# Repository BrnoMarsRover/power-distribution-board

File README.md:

# Power distribution board

Everything for the BrnoMarsRover power distribution board: the schematic and PCB, the
firmware that runs on it, and the ROS 2 driver that consumes it.

```
kicad/      schematic and PCB
pdf/        exported schematics
firmware/   Raspberry Pi Pico 2 sketch (Arduino, arduino-pico core)
ros2/       ROS 2 driver package (ament_python, Humble)
```

The firmware and the driver live together **because they share a versioned wire
protocol**. Every field name and status bit below is written twice - once in
`firmware/PowerBoard/Functions.cpp` and once in `ros2/powerboard/powerboard/powerboard_node.py`.
Splitting them across repositories would let the two halves be changed, reviewed and
deployed independently, and the failure mode is not a build error - it is silently
misparsed telemetry. Change the protocol in one commit, and bump `jsonSchemaVersion`
(firmware `Config.cpp`) together with `SUPPORTED_SCHEMA` (node) when you do.

## Hardware

Five INA238 current/voltage monitors on I2C, one per branch, each with a high-side
switch:

| Designator | I2C  | Shunt  | Rail             | Limit   |
|-----------|------|--------|------------------|---------|
| U2        | 0x40 | 3 mOhm | battery feed, and the master gate for the rest | 15 A |
| U3        | 0x41 | 5 mOhm | 24 V             | 2.5 A   |
| U4        | 0x42 | 5 mOhm | 15 V             | 4 A     |
| U5        | 0x43 | 5 mOhm | 12 V             | 5 A     |
| U6        | 0x44 | 5 mOhm | 5 V              | 12 A    |

Limits come from the 60 W rating of each DC-DC converter.

**Over-current protection ships disabled** (`ocpEnabled = false`). Some high-side
drivers were tripped by inrush and are bridged, so the board cannot actually switch
those branches off. Limits are still evaluated and reported, so an overload is visible
in telemetry even though nothing acts on it. `OCP ON` enables tripping if the hardware
is ever repaired.

Two things the board cannot measure, by construction:

- **Charging current.** The charger is wired on the battery side of U2's shunt, so
  charge current never crosses it. The driver infers charging from rising open-circuit
  voltage instead.
- **Currents above ~8 A on the INA CURRENT register**, which saturates there. The
  shunt-derived value is used for protection and for the `i` field because it has the
  range; `ir` is kept alongside it only for cross-checking.

## Serial protocol (schema v1)

USB CDC-ACM, one JSON object per line, telemetry at 2 Hz. Anything not starting with
`{` is human-readable diagnostics (`STATUS`, `RAW`) and is ignored by machine readers.

`"t"` gives the line type: `tel`, `evt`, `ack`, `err`, `info`.

### `tel` - periodic telemetry

```json
{"t":"tel","v":1,"seq":123,"up":61500,"ocp":0,"mst":1,"b":[ ... ]}
```

| Key   | Meaning                                        |
|-------|------------------------------------------------|
| `v`   | schema version                                  |
| `seq` | frame counter; gaps mean frames were lost       |
| `up`  | milliseconds since board boot                   |
| `ocp` | 1 if over-current protection is enabled         |
| `mst` | 1 if the U2 master branch is on                 |
| `b`   | one object per branch                           |

Each branch object:

| Key   | Unit | Meaning                                                   |
|-------|------|-----------------------------------------------------------|
| `n`   |      | designator, `U2`..`U6`                                    |
| `a`   |      | I2C address                                               |
| `s`   |      | status bits, see below                                    |
| `lim` | mA   | configured current limit                                  |
| `vb`  | V    | bus voltage                                               |
| `vs`  | mV   | shunt voltage                                             |
| `i`   | mA   | current derived from the shunt - **this is the real one** |
| `ir`  | mA   | INA CURRENT register, saturates at ~8 A, cross-check only |
| `tc`  | degC | INA die temperature                                       |
| `tr`  |      | cumulative trip count                                     |

Status bits in `s`:

| Bit  | Name        |
|------|-------------|
| 0x01 | online      |
| 0x02 | enabled     |
| 0x04 | tripped     |
| 0x08 | manual off  |
| 0x10 | powered     |
| 0x20 | over limit  |

### `evt` - pushed immediately, not on the telemetry tick

```json
{"t":"evt","up":61500,"ev":"over_limit","n":"U5","i":5200.0,"lim":5000,"ocp":0}
```

`ev` is one of `over_limit`, `over_limit_clear`, `ocp_trip`, `ocp_recover`. These are
pushed as they happen because with OCP disabled an over-limit event is the only
actionable signal the board can give.

### `ack` / `err` / `info`

```json
{"t":"ack","cmd":"JSON","msg":"json output"}
{"t":"err","cmd":"OFF U9","msg":"unknown branch"}
{"t":"info","fw":"...","v":1,"rails":5,"ocp":0}
```

### Commands (host to board, one per line)

| Command        | Effect                                          |
|----------------|-------------------------------------------------|
| `ON <U>`       | switch a branch on                              |
| `OFF <U>`      | switch a branch off                             |
| `OCP [ON|OFF]` | query or set over-current protection            |
| `RAW`          | dump every INA238 register, human readable      |
| `STATUS`       | human readable summary                          |
| `JSON`         | machine-readable output (the default)           |
| `HUMAN`        | switch to the plain-text table                  |
| `ONCE`         | emit a single telemetry frame                   |

## Firmware

Arduino sketch in `firmware/PowerBoard`, target Raspberry Pi Pico 2 (`rpipico2`),
arduino-pico core 5.5.1. Open `PowerBoard.ino` and flash it.

## ROS 2 driver

`ros2/powerboard`, ament_python, tested on Humble. Depends only on `rclpy`,
`std_msgs`, `sensor_msgs`, `diagnostic_msgs` and `python3-serial` - no custom
interfaces.

```bash
ros2 launch powerboard powerboard.launch.py
```

| Topic                | Type                       |
|----------------------|----------------------------|
| `~/battery`          | `sensor_msgs/BatteryState` |
| `~/rails/voltages`   | `std_msgs/Float32MultiArray` |
| `~/rails/currents`   | `std_msgs/Float32MultiArray` |
| `~/rails/powers`     | `std_msgs/Float32MultiArray` |
| `~/events`           | `std_msgs/String`          |
| `~/command`          | `std_msgs/String` (subscription, forwards any board command) |
| `/diagnostics`       | `diagnostic_msgs/DiagnosticArray` |

The rail arrays carry names in `layout.dim[i].label`, index-aligned with `data[i]`.

State of charge is estimated from a LiPo open-circuit-voltage curve, load-compensated
and smoothed, and published in `BatteryState.percentage`. It is a rough guide, not a
fuel gauge: between about 3.8 and 3.9 V/cell the curve is nearly flat, and below
3.7 V/cell it falls away sharply. Defaults assume Freya's **10S, 14.5 Ah** pack; see
`cell_count`, `design_capacity_ah` and `pack_resistance_ohm`.

**Only one process may hold the serial port.** Two readers steal bytes from each other,
which looks exactly like a flaky board - sequence gaps and a halved frame rate.

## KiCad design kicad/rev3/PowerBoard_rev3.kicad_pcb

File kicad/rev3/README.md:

# Power board rev3: KiCad 10 project

Open `PowerBoard_rev3.kicad_pro` in **KiCad 10**. The design spec lives in
[`docs/rev3/design.md`](../../docs/rev3/design.md), and every computed component value
comes from [`docs/rev3/rails.md`](../../docs/rev3/rails.md).

A review PDF is at [`pdf/rev3/PowerBoard_rev3_schematic.pdf`](../../pdf/rev3/PowerBoard_rev3_schematic.pdf).
The grouped BOM with part numbers is [`PowerBoard_rev3_bom.csv`](PowerBoard_rev3_bom.csv) (regenerate with `kicad-cli sch export bom`).
For the LCSC BOM tool, `python3 gen/bom_lcsc.py` turns it into [`PowerBoard_rev3_bom_lcsc.csv`](PowerBoard_rev3_bom_lcsc.csv) (MPN + manufacturer, no PCB-only items).

## How the schematic was made

`gen/build.py` generated it from the design data, so nothing was drawn by hand from
scratch:

```
python3 kicad/rev3/gen/build.py
```

That run does six things:

1. Writes the custom symbols (`PowerBoard_rev3.kicad_sym`).
2. Writes the custom footprints (`PowerBoard_rev3.pretty`).
3. Writes the 14 sheets.
4. Upgrades every file to the KiCad 10 format with `kicad-cli` (KiCad 10 from the `kicad-10.0-releases` PPA).
5. Runs ERC.
6. Exports KiCad's own netlist and checks it pin by pin against the netlist the script
   intended.

Result at generation time:
- 520 parts and 281 nets.
- Netlist check passes.
- ERC is clean at every severity.

Every sheet is drawn like a hand-made schematic: parts sit at chosen positions and real
wires connect them.
- Power flows left to right along the rails. Converters and drivers sit below their power
  path, with their setting parts below or beside them.
- Labels appear only where a signal leaves the sheet. The exception is the ESP32 module,
  whose GPIOs carry labels in the usual way, while the circuits around it (reset, boot,
  USB, host UART, LEDs, sense dividers) are drawn out.
- On the outputs sheet each rail is a column: a bus with one row per output (PTC,
  connector, GND).

The drawing goes through the same netlist check, so a wire landing where it shouldn't is
caught before anyone opens KiCad. One crossing is intentional: on the `can` sheet, CANH
crosses CANL without a junction on its way to the second connector.

## Board rules

`gen/board_rules.py` sets up the PCB side for JLCPCB's 4-layer process with 2 oz outer copper
(the one paid option):
- **Stackup:** 1.6 mm, JLC04161H-7628, 2 oz outer / 0.5 oz inner, HASL lead-free.
- **Limits:** 0.25 mm minimum track, 0.15 mm clearance, 0.25 mm annular ring (vias 0.9 / 0.4 mm
  and up), 1.0 mm silkscreen text.
- **Netclasses** for the 42 V, 54 V and rail nets, and a 0.5 mm clearance on the outer
  layers around 42 / 54 V pours.

It writes the rules into `PowerBoard_rev3.kicad_pro` and `PowerBoard_rev3.kicad_dru`.
It creates `PowerBoard_rev3.kicad_pcb` only if the board doesn't exist yet, so re-running
it never touches a layout. The values and the reasons for them are in
`docs/rev3/design.md`, section 8.

**Once you start editing in KiCad, these files are the source of truth.** Re-running
`build.py` overwrites them. The generator is a bootstrap, not a build step.

## Sheets

| Sheet | Contents |
|-------|----------|
| `power_in` | Battery XT90 input, SMCJ45A, bulk capacitance, 2 mΩ Kelvin shunt (Bourns CSS2H-2512K) with INA228, charger input XT60 and pack charge-port XT60 (charging flows through the shunt) |
| `sw_42d`, `sw_42c` | 42 V drive group and converter-feed group eFuses (TPS48111-Q1, 2 + 1 D2PAK). The drive group has the motor-switch kill FET on EN/UVLO. |
| `sw_24`, `sw_12`, `sw_5` | Rail eFuses, input TVS, bulk capacitance, input and output voltage sense |
| `sw_54` | eFuse in front of the 54 V boost |
| `brake` | Brake chopper on OUT42D: TLV1805 + LM4040 comparator (on 47.5 V, off 45 V), IPB042N10N3G, XT60 to an off-board braking resistor, BRAKE_ACT to the ESP32 |
| `outputs` | Rail input connectors, 8 × XT90 outputs, and the 24 / 12 / 5 V outputs with their PTCs. JST-XH 54 V output to the Zyxel |
| `boost54` | LM5122 boost, 30–42 V to 54 V, 100 W |
| `aux_power` | LM5017 (42 V to 5.3 V, constant on-time with ripple injection), the diode-OR with USB VBUS, and the AP7361C 3.3 V LDO |
| `mcu` | ESP32-S3-WROOM-1U, USB-C with ESD, host UART on JST-GH, buttons, LEDs, NTC |
| `can` | TCAN1044AV, split termination on solder jumpers, two Molex CLIK-Mate 4p CAN connectors matching the EPOS4 50/5 (X11 / X12) |
| `io` | TCA9535 (switch control), 2 × ADC128D818, motor-switch latch (74LVC1G74) and the rear-panel switch input |

## Custom parts

- **Symbols:** TPS48111-Q1, LM5122, LM5017, TLV1805, TCAN1044AV and INA228, with pinouts taken
  from the TI datasheets.
  - Their pins are arranged for the drawing. For example, the INA228 sense inputs sit on
    top, 5.08 mm apart under the shunt's sense pins, so the Kelvin lines drop straight down.
  - Q_NMOS_GDS covers the D2PAK and DPAK FETs: KiCad 10 dropped its GDS-numbered FET
    symbols.
- **Footprints:** R_Bourns_CSS2H-2512_Kelvin is Bourns' 4-terminal land pattern as a
  net-tie footprint. TI_DGX0019A_VSSOP-19 is drawn from TI's land pattern, with pads
  lengthened for hand soldering. XT90PB-M, XT90PB-F and DEANS-T are copied from rev2's
  SamacSys library.

## Review before layout

These are the things the generator could not settle on its own:

- [ ] **LM5122 loop.** R_SLOPE and the COMP–FB Type 2 network are computed in `rails.py`
  (crossover 8–11 kHz). Confirm on the bench with a load step from 0.2 to 1.8 A: the
  response should be damped, with no ringing.
- [x] **Pre-charge FET SOA.** Ramps were cut to stay inside the IPB042N10N3G's DC SOA
  (0.4 A at 42 V). See `docs/rev3/design.md` 4.3.
- [ ] **Bypass-link placement.** Put each eFuse's two bypass holes (M4 on the 42 V groups,
  M3 elsewhere) where a copper strip can be bolted across with the board in the rover,
  and silkscreen "BYPASS: no protection, battery off to fit".
- [ ] **EPOS4 input capacitance.** maxon doesn't publish it. Measure one drive: it sets the
  pre-charge ramp time (470 µF per drive is assumed).
- [ ] **Brake resistor.** Size the off-board resistor (10 Ω / 100 W assumed) to the
  rover's braking energy.
- [x] **Boost inductor footprint.** Coilcraft MSS1583-223MED on KiCad's `L_Coilcraft_MSS1583-XXX`.
- [ ] **Aux buck (LM5017).** On first power-up, check the switching frequency (about
  400 kHz) and that the FB ripple is clean, with no bursts of pulses followed by long gaps.
  Then check the output at 0 and 0.5 A. The Type 3 ripple values are TI's starting point.
- [ ] **Connector footprints.** XT90 and Deans: check the M and F pin geometry against the
  Amass drawings. For every power connector, check that footprint pin 1 is the housing's
  + side.
- [ ] **Electrolytic sizes.** 100 µF / 100 V and 100 µF / 80 V parts may need a larger
  footprint than `CP_Elec_10x10.5`.
- [ ] **Hand-solder holes.** Add a 1–1.5 mm plated hole through the exposed pads of the
  LM5122, the LM5017 and the ESP32 module (layout step).
- [ ] **Placement.** Put the MMBT3904 temperature sensors against their main FETs, and
  route every shunt Kelvin.
- [ ] **ESD arrays are flow-through.** On both USBLC6-2SC6, pins 1/6 and 3/4 are joined
  inside the part. The connector side and the MCU side are therefore separate nets, which
  forces each line across its pad pair in layout.

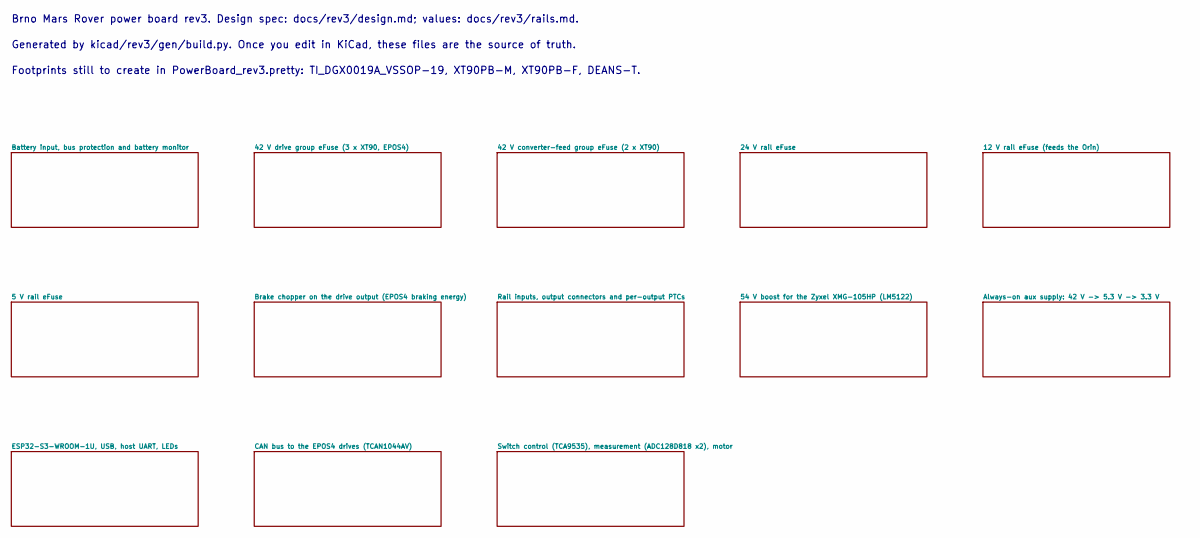
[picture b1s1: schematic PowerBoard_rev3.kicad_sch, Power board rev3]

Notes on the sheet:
Brno Mars Rover power board rev3. Design spec: docs/rev3/design.md; values: docs/rev3/rails.md.
Footprints still to create in PowerBoard_rev3.pretty: TI_DGX0019A_VSSOP-19, XT90PB-M, XT90PB-F, DEANS-T.
Generated by kicad/rev3/gen/build.py. Once you edit in KiCad, these files are the source of truth.

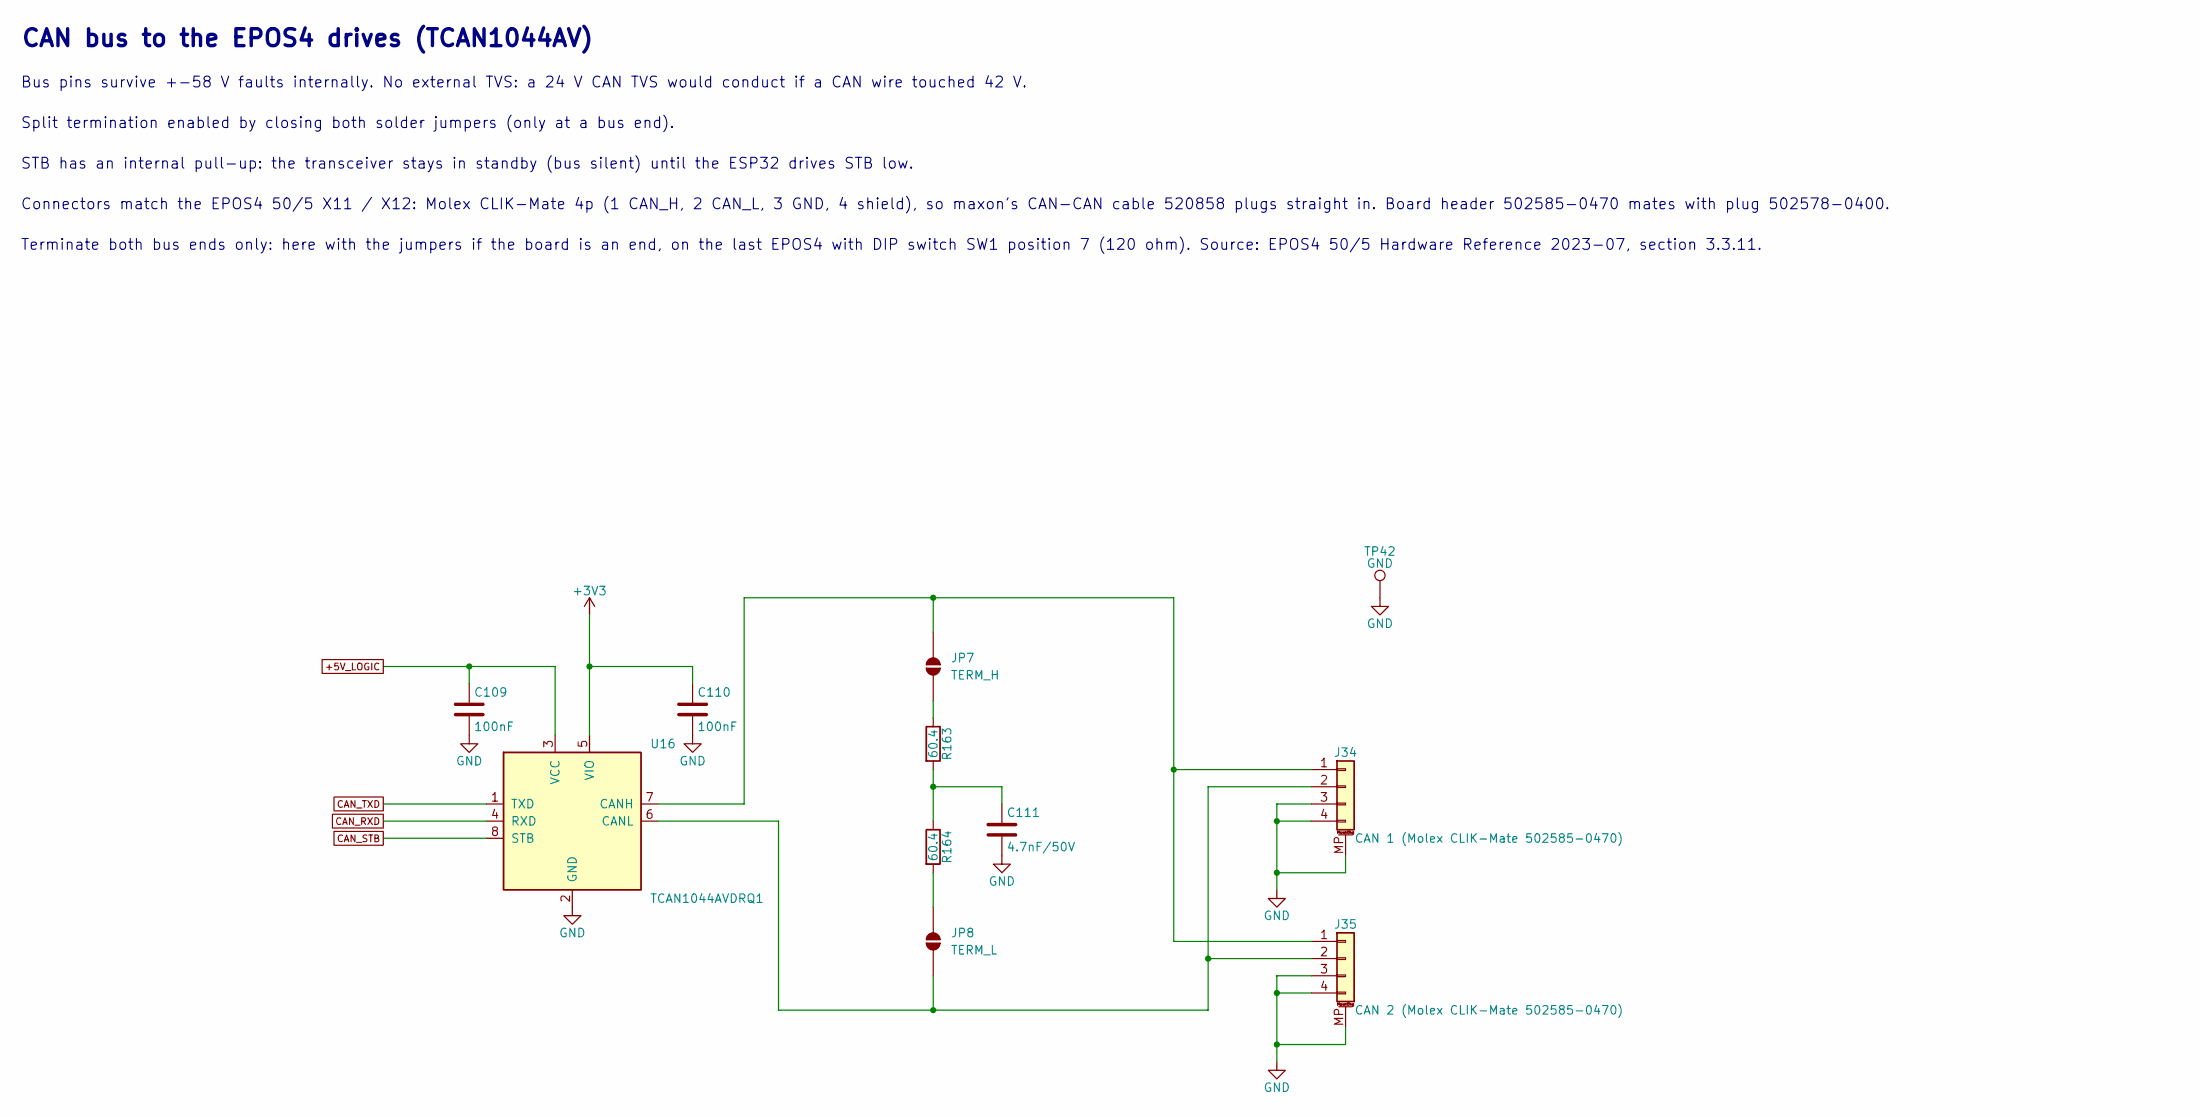
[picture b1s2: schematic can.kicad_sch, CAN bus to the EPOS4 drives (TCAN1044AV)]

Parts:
C109, C110: 100nF; C_0603_1608Metric_Pad1.08x0.95mm_HandSolder; MPN C0603C104K5RACTU
C111: 4.7nF/50V; C_0603_1608Metric_Pad1.08x0.95mm_HandSolder; MPN CL10B472KB8NNNC
J34: CAN 1 (Molex CLIK-Mate 502585-0470); Molex_CLIK-Mate_502585-0470_1x04-1MP_P1.50mm_Horizontal; MPN 502585-0470
J35: CAN 2 (Molex CLIK-Mate 502585-0470); Molex_CLIK-Mate_502585-0470_1x04-1MP_P1.50mm_Horizontal; MPN 502585-0470
JP7: TERM_H; SolderJumper-2_P1.3mm_Open_Pad1.0x1.5mm; MPN none: PCB solder jumper
JP8: TERM_L; SolderJumper-2_P1.3mm_Open_Pad1.0x1.5mm; MPN none: PCB solder jumper
R163, R164: 60.4; R_0805_2012Metric_Pad1.20x1.40mm_HandSolder; MPN ERJ-6ENF60R4V
TP42: GND; TestPoint_Keystone_5015_Micro_Mini; MPN 5015
U16: TCAN1044AVDRQ1; SOIC-8_3.9x4.9mm_P1.27mm; MPN TCAN1044AVDRQ1

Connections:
+3V3: C110.1, U16.5 (VIO); also elsewhere on the board
+5V_LOGIC: C109.1, U16.3 (VCC); also elsewhere on the board
CAN_RXD: U16.4 (RXD); also elsewhere on the board
CAN_STB: U16.8 (STB); also elsewhere on the board
CAN_TXD: U16.1 (TXD); also elsewhere on the board
GND: C109.2, C110.2, C111.2, J34.3, J34.4, J34.MP (MountPin), J35.3, J35.4, J35.MP (MountPin), TP42.1, U16.2 (GND); also elsewhere on the board
unnamed: C111.1, R163.2, R164.1
unnamed: J34.1, J35.1, JP7.1 (A), U16.7 (CANH)
unnamed: J34.2, J35.2, JP8.1 (A), U16.6 (CANL)
unnamed: JP7.2 (B), R163.1
unnamed: JP8.2 (B), R164.2

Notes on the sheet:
Bus pins survive +-58 V faults internally. No external TVS: a 24 V CAN TVS would conduct if a CAN wire touched 42 V.
Split termination enabled by closing both solder jumpers (only at a bus end).
Terminate both bus ends only: here with the jumpers if the board is an end, on the last EPOS4 with DIP switch SW1 position 7 (120 ohm). Source: EPOS4 50/5 Hardware Reference 2023-07, section 3.3.11.
CAN bus to the EPOS4 drives (TCAN1044AV)
Connectors match the EPOS4 50/5 X11 / X12: Molex CLIK-Mate 4p (1 CAN_H, 2 CAN_L, 3 GND, 4 shield), so maxon's CAN-CAN cable 520858 plugs straight in. Board header 502585-0470 mates with plug 502578-0400.
STB has an internal pull-up: the transceiver stays in standby (bus silent) until the ESP32 drives STB low.

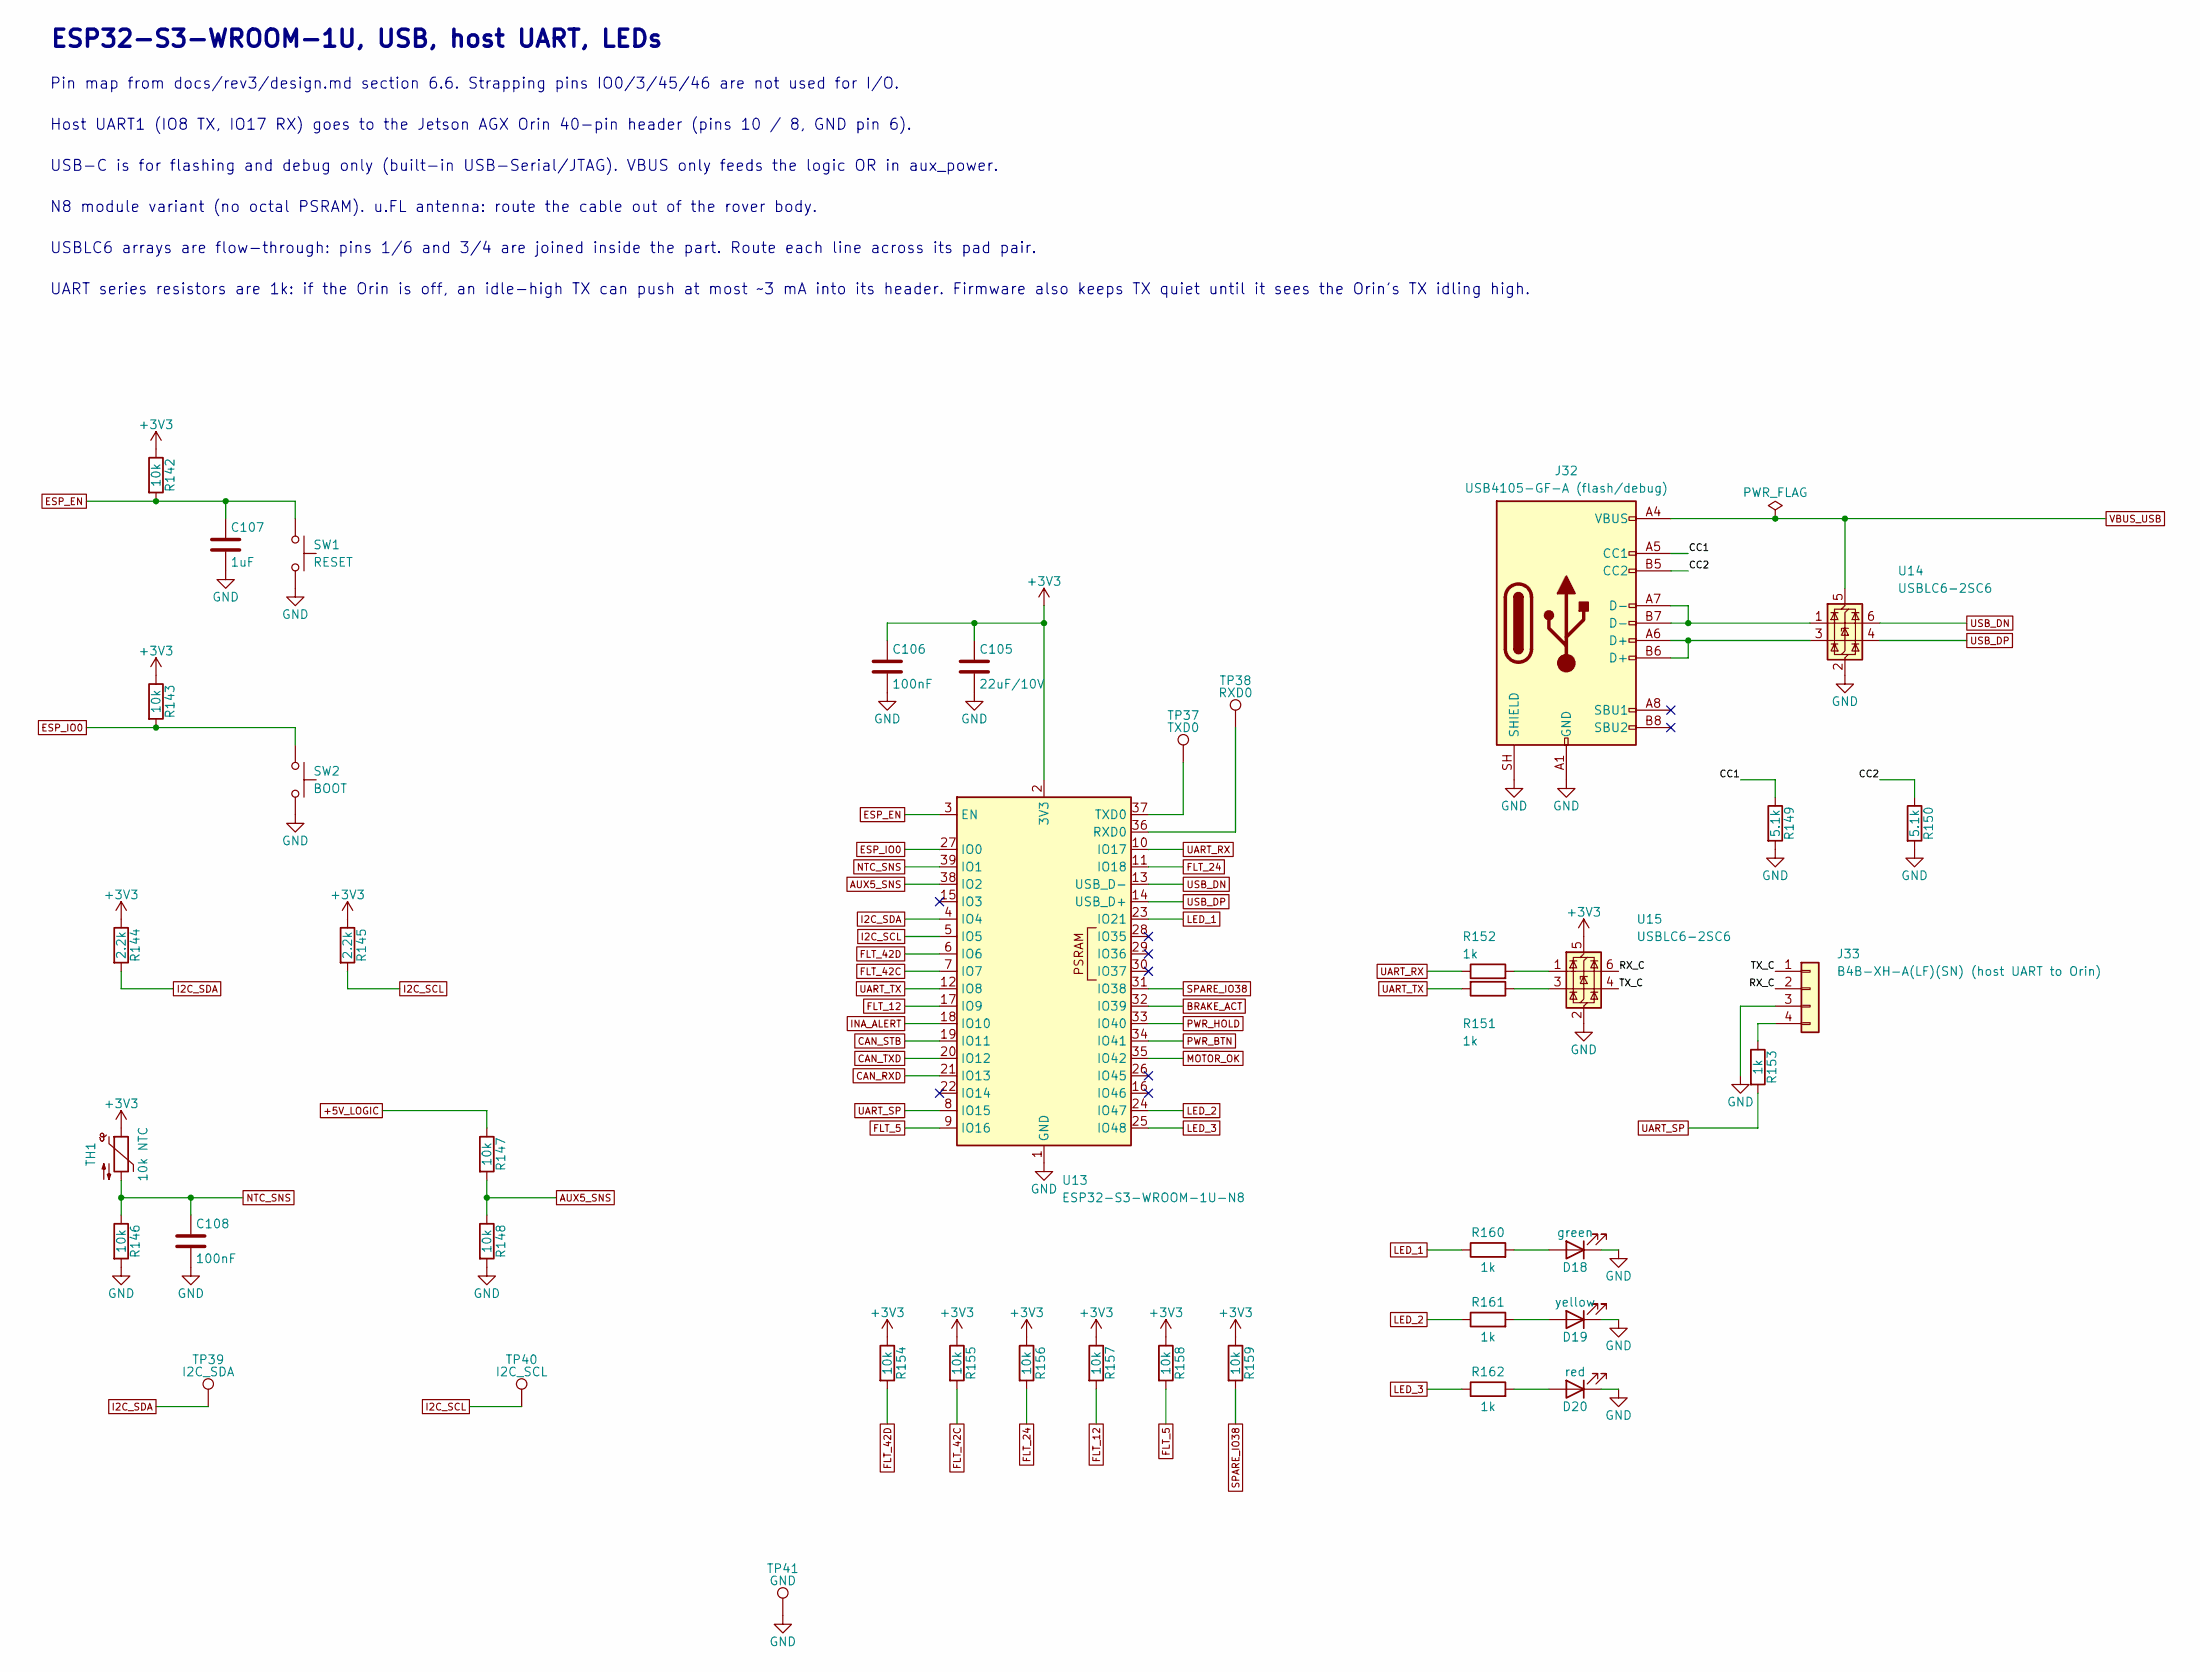
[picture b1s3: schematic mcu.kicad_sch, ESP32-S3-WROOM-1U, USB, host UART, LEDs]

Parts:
C105: 22uF/10V; C_1206_3216Metric_Pad1.33x1.80mm_HandSolder; MPN CL31B226KPHNNNE
C106, C108: 100nF; C_0603_1608Metric_Pad1.08x0.95mm_HandSolder; MPN C0603C104K5RACTU
C107: 1uF; C_0603_1608Metric_Pad1.08x0.95mm_HandSolder; MPN C0603C105K3RACTU
D18: green; LED_0805_2012Metric_Pad1.15x1.40mm_HandSolder; MPN APT2012SGC
D19: yellow; LED_0805_2012Metric_Pad1.15x1.40mm_HandSolder; MPN APT2012SYCK
D20: red; LED_0805_2012Metric_Pad1.15x1.40mm_HandSolder; MPN APT2012SURCK
J32: USB4105-GF-A (flash/debug); USB_C_Receptacle_GCT_USB4105-GF-A_2oz; MPN USB4105-GF-A
J33: B4B-XH-A(LF)(SN) (host UART to Orin); JST_XH_B4B-XH-A_1x04_P2.50mm_Vertical; MPN B4B-XH-A(LF)(SN)
R142, R143, R146, R147, R148, R154, R155, R156, R157, R158, R159: 10k; R_0603_1608Metric_Pad0.98x0.95mm_HandSolder; MPN RC0603FR-0710KL
R144, R145: 2.2k; R_0603_1608Metric_Pad0.98x0.95mm_HandSolder; MPN RC0603FR-072K2L
R149, R150: 5.1k; R_0603_1608Metric_Pad0.98x0.95mm_HandSolder; MPN RC0603FR-075K1L
R151, R152, R153, R160, R161, R162: 1k; R_0603_1608Metric_Pad0.98x0.95mm_HandSolder; MPN RC0603FR-071KL
SW1: RESET; SW_SPST_TL3342; MPN TL3342F160QG
SW2: BOOT; SW_SPST_TL3342; MPN TL3342F160QG
TH1: 10k NTC; R_0603_1608Metric_Pad0.98x0.95mm_HandSolder; MPN NCP18XH103F03RB
TP37: TXD0; TestPoint_Pad_D1.5mm; MPN none: PCB pad
TP38: RXD0; TestPoint_Pad_D1.5mm; MPN none: PCB pad
TP39: I2C_SDA; TestPoint_Pad_D1.5mm; MPN none: PCB pad
TP40: I2C_SCL; TestPoint_Pad_D1.5mm; MPN none: PCB pad
TP41: GND; TestPoint_Keystone_5015_Micro_Mini; MPN 5015
U13: ESP32-S3-WROOM-1U-N8; ESP32-S3-WROOM-1U_HandSolder; MPN ESP32-S3-WROOM-1U-N8
U14, U15: USBLC6-2SC6; SOT-23-6; MPN USBLC6-2SC6

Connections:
+3V3: C105.1, C106.1, R142.1, R143.1, R144.1, R145.1, R154.1, R155.1, R156.1, R157.1, R158.1, R159.1, TH1.1, U13.2 (3V3), U15.5 (VBUS); also elsewhere on the board
+5V_LOGIC: R147.1; also elsewhere on the board
/ESP32-S3-WROOM-1U, USB, host UART, LEDs/CC1: J32.A5 (CC1), R149.1
/ESP32-S3-WROOM-1U, USB, host UART, LEDs/CC2: J32.B5 (CC2), R150.1
/ESP32-S3-WROOM-1U, USB, host UART, LEDs/RX_C: J33.2, U15.6 (I/O1)
/ESP32-S3-WROOM-1U, USB, host UART, LEDs/TX_C: J33.1, U15.4 (I/O2)
AUX5_SNS: R147.2, R148.1, U13.38 (IO2)
BRAKE_ACT: U13.32 (IO39); also elsewhere on the board
CAN_RXD: U13.21 (IO13); also elsewhere on the board
CAN_STB: U13.19 (IO11); also elsewhere on the board
CAN_TXD: U13.20 (IO12); also elsewhere on the board
ESP_EN: C107.1, R142.2, SW1.1, U13.3 (EN)
ESP_IO0: R143.2, SW2.1, U13.27 (IO0)
FLT_5: R158.2, U13.9 (IO16); also elsewhere on the board
FLT_12: R157.2, U13.17 (IO9); also elsewhere on the board
FLT_24: R156.2, U13.11 (IO18); also elsewhere on the board
FLT_42C: R155.2, U13.7 (IO7); also elsewhere on the board
FLT_42D: R154.2, U13.6 (IO6); also elsewhere on the board
GND: C105.2, C106.2, C107.2, C108.2, D18.1 (K), D19.1 (K), D20.1 (K), J32.A1 (GND), J32.A12 (GND), J32.B1 (GND), J32.B12 (GND), J32.SH (SHIELD), J33.3, R146.2, R148.2, R149.2, R150.2, SW1.2, SW2.2, TP41.1, U13.1 (GND), U13.40 (GND), U13.41 (GND), U14.2 (GND), U15.2 (GND); also elsewhere on the board
I2C_SCL: R145.2, TP40.1, U13.5 (IO5); also elsewhere on the board
I2C_SDA: R144.2, TP39.1, U13.4 (IO4); also elsewhere on the board
INA_ALERT: U13.18 (IO10); also elsewhere on the board
LED_1: R160.1, U13.23 (IO21)
LED_2: R161.1, U13.24 (IO47)
LED_3: R162.1, U13.25 (IO48)
MOTOR_OK: U13.35 (IO42); also elsewhere on the board
NTC_SNS: C108.1, R146.1, TH1.2, U13.39 (IO1)
unnamed: D18.2 (A), R160.2
unnamed: D19.2 (A), R161.2
unnamed: D20.2 (A), R162.2
unnamed: J32.A6 (D+), J32.B6 (D+), U14.3 (I/O2)
unnamed: J32.A7 (D-), J32.B7 (D-), U14.1 (I/O1)
unnamed: J33.4, R153.1
unnamed: R151.1, U15.3 (I/O2)
unnamed: R152.2, U15.1 (I/O1)
unnamed: TP38.1, U13.36 (RXD0)
unnamed: TP37.1, U13.37 (TXD0)
PWR_BTN: U13.34 (IO41); also elsewhere on the board
PWR_HOLD: U13.33 (IO40); also elsewhere on the board
SPARE_IO38: R159.2, U13.31 (IO38)
UART_RX: R152.1, U13.10 (IO17)
UART_SP: R153.2, U13.8 (IO15)
UART_TX: R151.2, U13.12 (IO8)
USB_DN: U13.13 (USB_D-), U14.6 (I/O1)
USB_DP: U13.14 (USB_D+), U14.4 (I/O2)
VBUS_USB: J32.A4 (VBUS), J32.A9 (VBUS), J32.B4 (VBUS), J32.B9 (VBUS), U14.5 (VBUS); also elsewhere on the board

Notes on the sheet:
UART series resistors are 1k: if the Orin is off, an idle-high TX can push at most ~3 mA into its header. Firmware also keeps TX quiet until it sees the Orin's TX idling high.
USB-C is for flashing and debug only (built-in USB-Serial/JTAG). VBUS only feeds the logic OR in aux_power.
Host UART1 (IO8 TX, IO17 RX) goes to the Jetson AGX Orin 40-pin header (pins 10 / 8, GND pin 6).
ESP32-S3-WROOM-1U, USB, host UART, LEDs
USBLC6 arrays are flow-through: pins 1/6 and 3/4 are joined inside the part. Route each line across its pad pair.
Pin map from docs/rev3/design.md section 6.6. Strapping pins IO0/3/45/46 are not used for I/O.
N8 module variant (no octal PSRAM). u.FL antenna: route the cable out of the rover body.

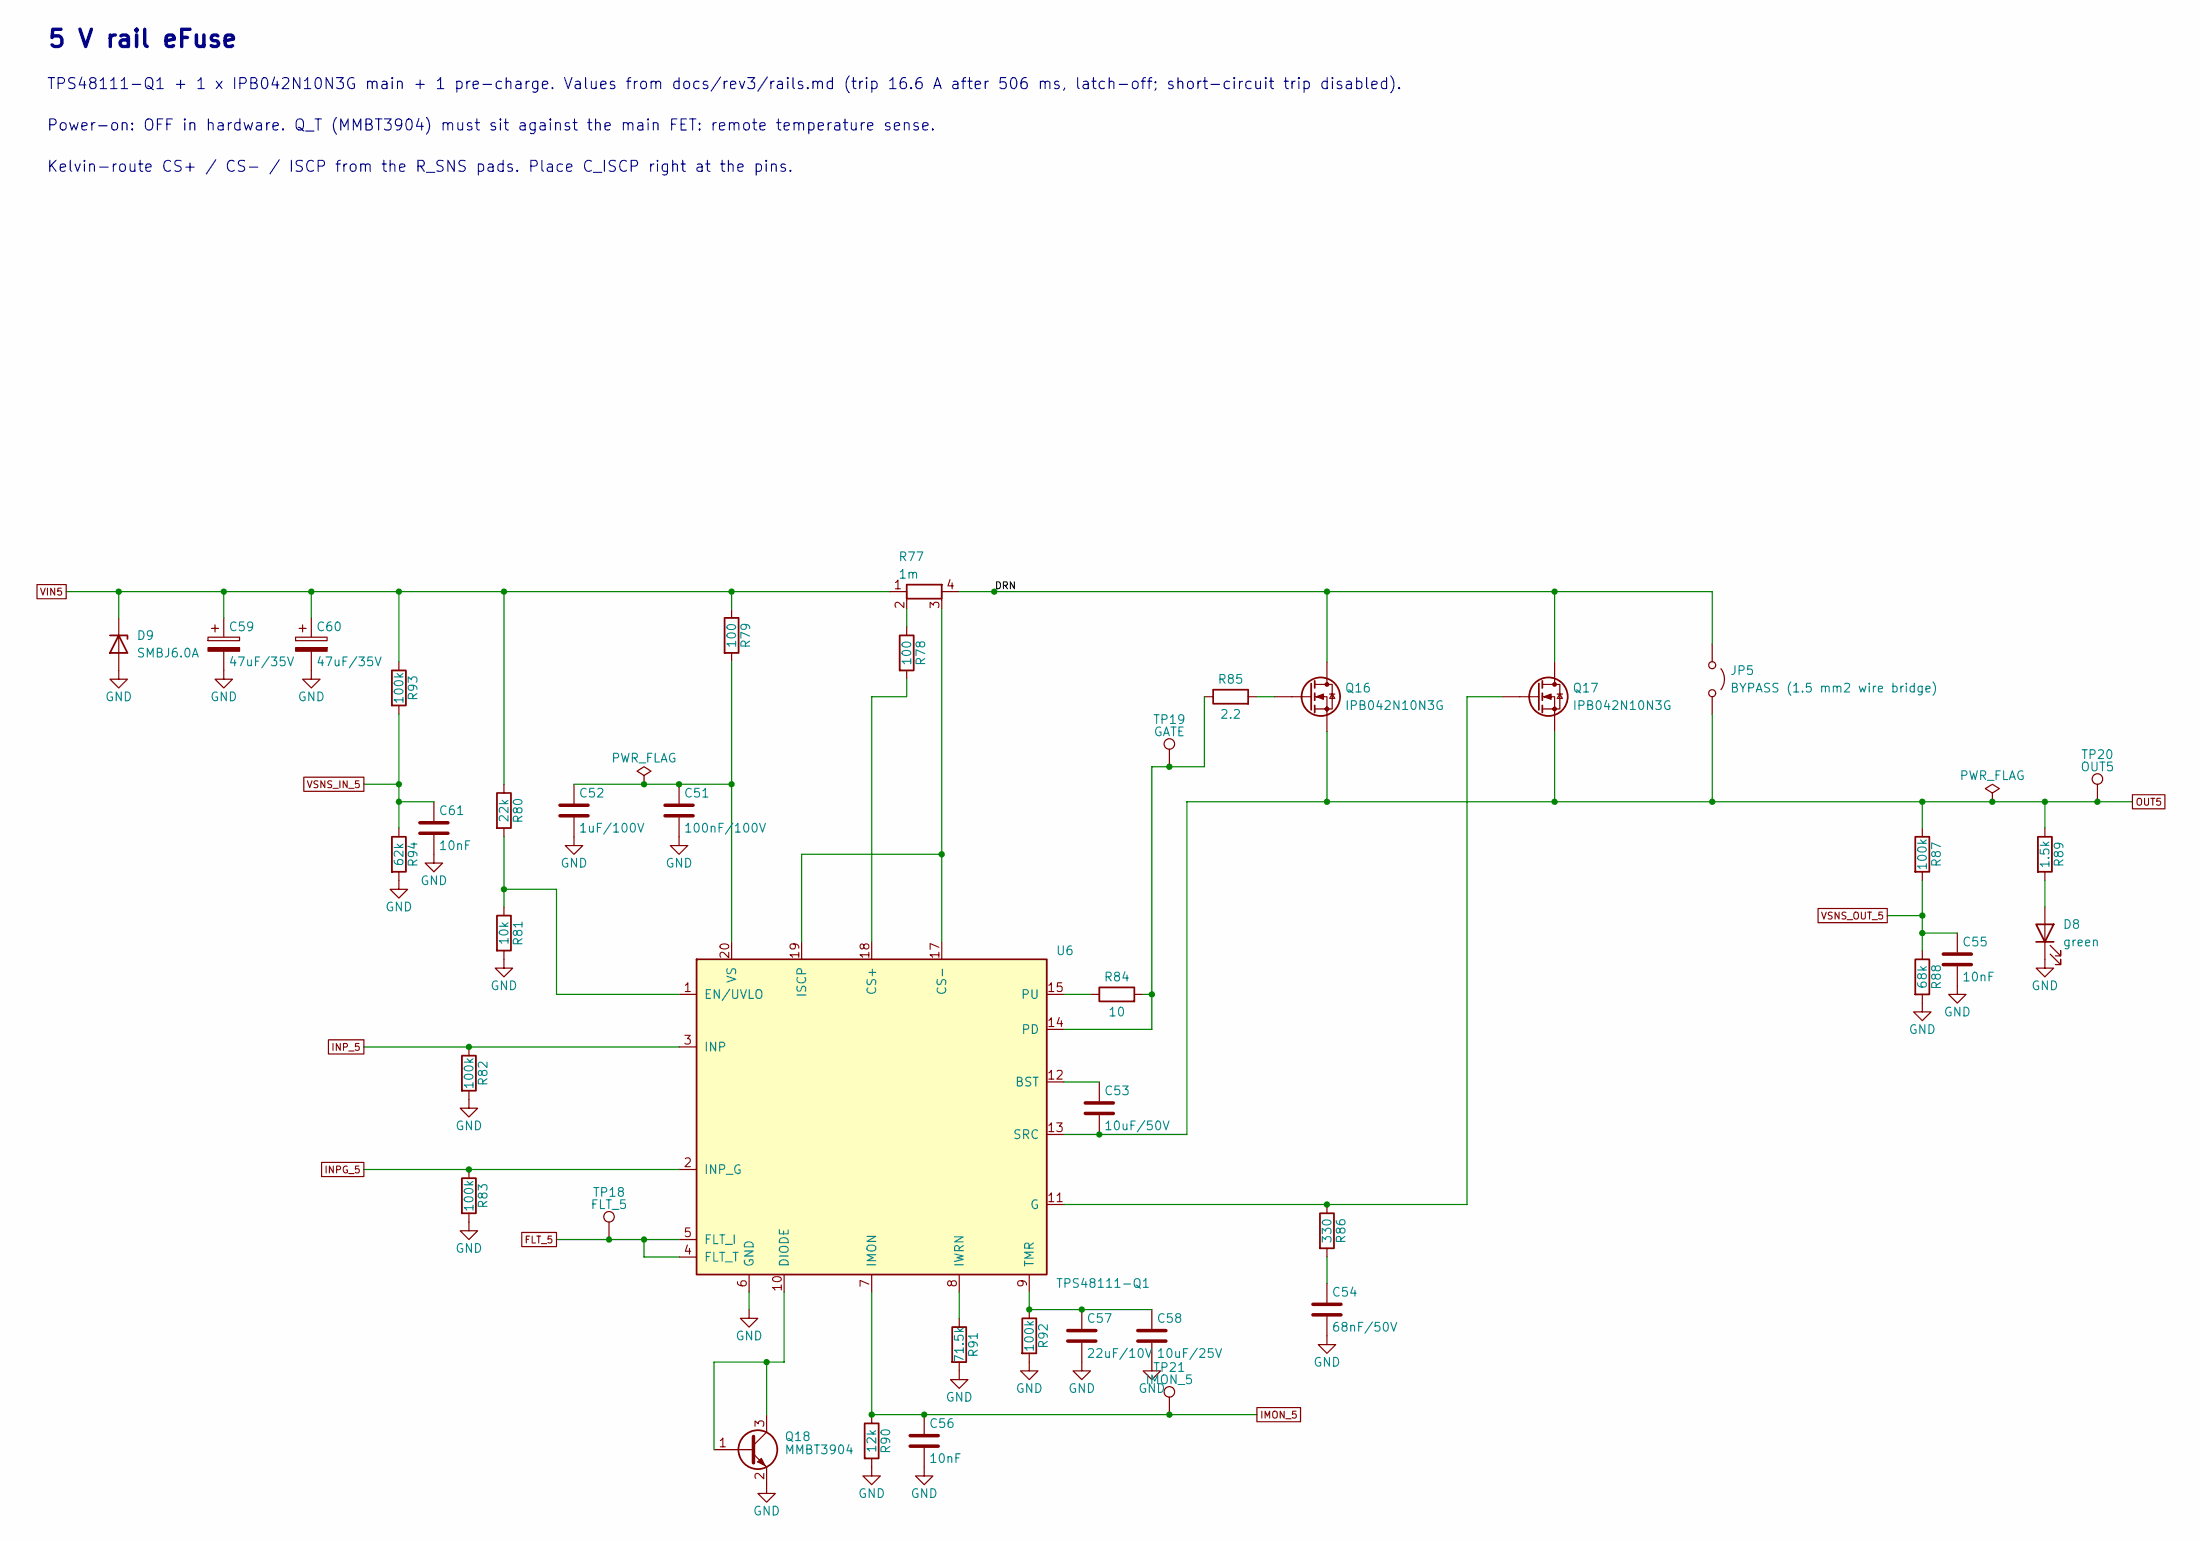
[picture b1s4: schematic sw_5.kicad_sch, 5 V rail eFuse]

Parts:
C51: 100nF/100V; C_0603_1608Metric_Pad1.08x0.95mm_HandSolder; MPN CL10B104KC8NNNC
C52: 1uF/100V; C_1206_3216Metric_Pad1.33x1.80mm_HandSolder; MPN GRM31CR72A105KA01L
C53: 10uF/50V; C_1210_3225Metric_Pad1.33x2.70mm_HandSolder; MPN CL32B106KBJNNNE
C54: 68nF/50V; C_1206_3216Metric_Pad1.33x1.80mm_HandSolder; MPN C1206C683K5RACTU
C55, C56, C61: 10nF; C_0603_1608Metric_Pad1.08x0.95mm_HandSolder; MPN CL10B103KB8NNNC
C57: 22uF/10V; C_1206_3216Metric_Pad1.33x1.80mm_HandSolder; MPN CL31B226KPHNNNE
C58: 10uF/25V; C_1206_3216Metric_Pad1.33x1.80mm_HandSolder; MPN CL31A106KAHNNNE
C59, C60: 47uF/35V; CP_Radial_D6.3mm_P2.50mm; MPN EEU-FC1V470
D8: green; LED_0805_2012Metric_Pad1.15x1.40mm_HandSolder; MPN APT2012SGC
D9: SMBJ6.0A; D_SMB; MPN SMBJ6.0A
JP5: BYPASS (1.5 mm2 wire bridge); WireBridge_1.5mm2_P5.08mm; MPN none: solid copper wire bridge, fitted 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
Q16, Q17: IPB042N10N3G; TO-263-2; MPN IPB042N10N3GATMA1
Q18: MMBT3904; SOT-23; MPN MMBT3904LT1G
R77: 1m; R_Bourns_CSS2H-2512_Kelvin; MPN CSS2H-2512R-1L00F
R78, R79: 100; R_0603_1608Metric_Pad0.98x0.95mm_HandSolder; MPN RC0603FR-07100RL
R80: 22k; R_0603_1608Metric_Pad0.98x0.95mm_HandSolder; MPN RC0603FR-0722KL
R81: 10k; R_0603_1608Metric_Pad0.98x0.95mm_HandSolder; MPN RC0603FR-0710KL
R82, R83, R87, R92, R93: 100k; R_0603_1608Metric_Pad0.98x0.95mm_HandSolder; MPN RC0603FR-07100KL
R84: 10; R_0603_1608Metric_Pad0.98x0.95mm_HandSolder; MPN RC0603FR-0710RL
R85: 2.2; R_0603_1608Metric_Pad0.98x0.95mm_HandSolder; MPN RC0603FR-072R2L
R86: 330; R_0603_1608Metric_Pad0.98x0.95mm_HandSolder; MPN RC0603FR-07330RL
R88: 68k; R_0603_1608Metric_Pad0.98x0.95mm_HandSolder; MPN RC0603FR-0768KL
R89: 1.5k; R_0603_1608Metric_Pad0.98x0.95mm_HandSolder; MPN RC0603FR-071K5L
R90: 12k; R_0603_1608Metric_Pad0.98x0.95mm_HandSolder; MPN RC0603FR-0712KL
R91: 71.5k; R_0603_1608Metric_Pad0.98x0.95mm_HandSolder; MPN RC0603FR-1371K5L
R94: 62k; R_0603_1608Metric_Pad0.98x0.95mm_HandSolder; MPN RC0603FR-0762KL
TP18: FLT_5; TestPoint_Pad_D1.5mm; MPN none: PCB pad
TP19: GATE; TestPoint_Pad_D1.5mm; MPN none: PCB pad
TP20: OUT5; TestPoint_Pad_D1.5mm; MPN none: PCB pad
TP21: IMON_5; TestPoint_Pad_D1.5mm; MPN none: PCB pad
U6: TPS48111-Q1; TI_DGX0019A_VSSOP-19; MPN TPS48111LQDGXRQ1

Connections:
/5 V rail eFuse/DRN: JP5.1 (A), Q16.2 (D), Q17.2 (D), R77.4
FLT_5: TP18.1, U6.4 (FLT_T), U6.5 (FLT_I); also elsewhere on the board
GND: C51.2, C52.2, C54.2, C55.2, C56.2, C57.2, C58.2, C59.2, C60.2, C61.2, D8.1 (K), D9.2 (A), Q18.2 (E), R81.2, R82.2, R83.2, R88.2, R90.2, R91.2, R92.2, R94.2, U6.6 (GND); also elsewhere on the board
IMON_5: C56.1, R90.1, TP21.1, U6.7 (IMON); also elsewhere on the board
INPG_5: R83.1, U6.2 (INP_G); also elsewhere on the board
INP_5: R82.1, U6.3 (INP); also elsewhere on the board
unnamed: C54.1, R86.2
unnamed: D8.2 (A), R89.2
unnamed: Q16.1 (G), R85.2
unnamed: Q17.1 (G), R86.1, U6.11 (G)
unnamed: Q18.1 (B), Q18.3 (C), U6.10 (DIODE)
unnamed: R77.2, R78.1
unnamed: C53.1, U6.12 (BST)
unnamed: R78.2, U6.18 (CS+)
unnamed: R77.3, U6.17 (CS-), U6.19 (ISCP)
unnamed: R80.2, R81.1, U6.1 (EN/UVLO)
unnamed: R91.1, U6.8 (IWRN)
unnamed: R84.2, R85.1, TP19.1, U6.14 (PD)
unnamed: R84.1, U6.15 (PU)
unnamed: C57.1, C58.1, R92.1, U6.9 (TMR)
unnamed: C51.1, C52.1, R79.2, U6.20 (VS)
OUT5: C53.2, JP5.2 (B), Q16.3 (S), Q17.3 (S), R87.1, R89.1, TP20.1, U6.13 (SRC); also elsewhere on the board
VIN5: C59.1, C60.1, D9.1 (K), R77.1, R79.1, R80.1, R93.1; also elsewhere on the board
VSNS_IN_5: C61.1, R93.2, R94.1; also elsewhere on the board
VSNS_OUT_5: C55.1, R87.2, R88.1; also elsewhere on the board

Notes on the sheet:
Power-on: OFF in hardware. Q_T (MMBT3904) must sit against the main FET: remote temperature sense.
Kelvin-route CS+ / CS- / ISCP from the R_SNS pads. Place C_ISCP right at the pins.
5 V rail eFuse
TPS48111-Q1 + 1 x IPB042N10N3G main + 1 pre-charge. Values from docs/rev3/rails.md (trip 16.6 A after 506 ms, latch-off; short-circuit trip disabled).
